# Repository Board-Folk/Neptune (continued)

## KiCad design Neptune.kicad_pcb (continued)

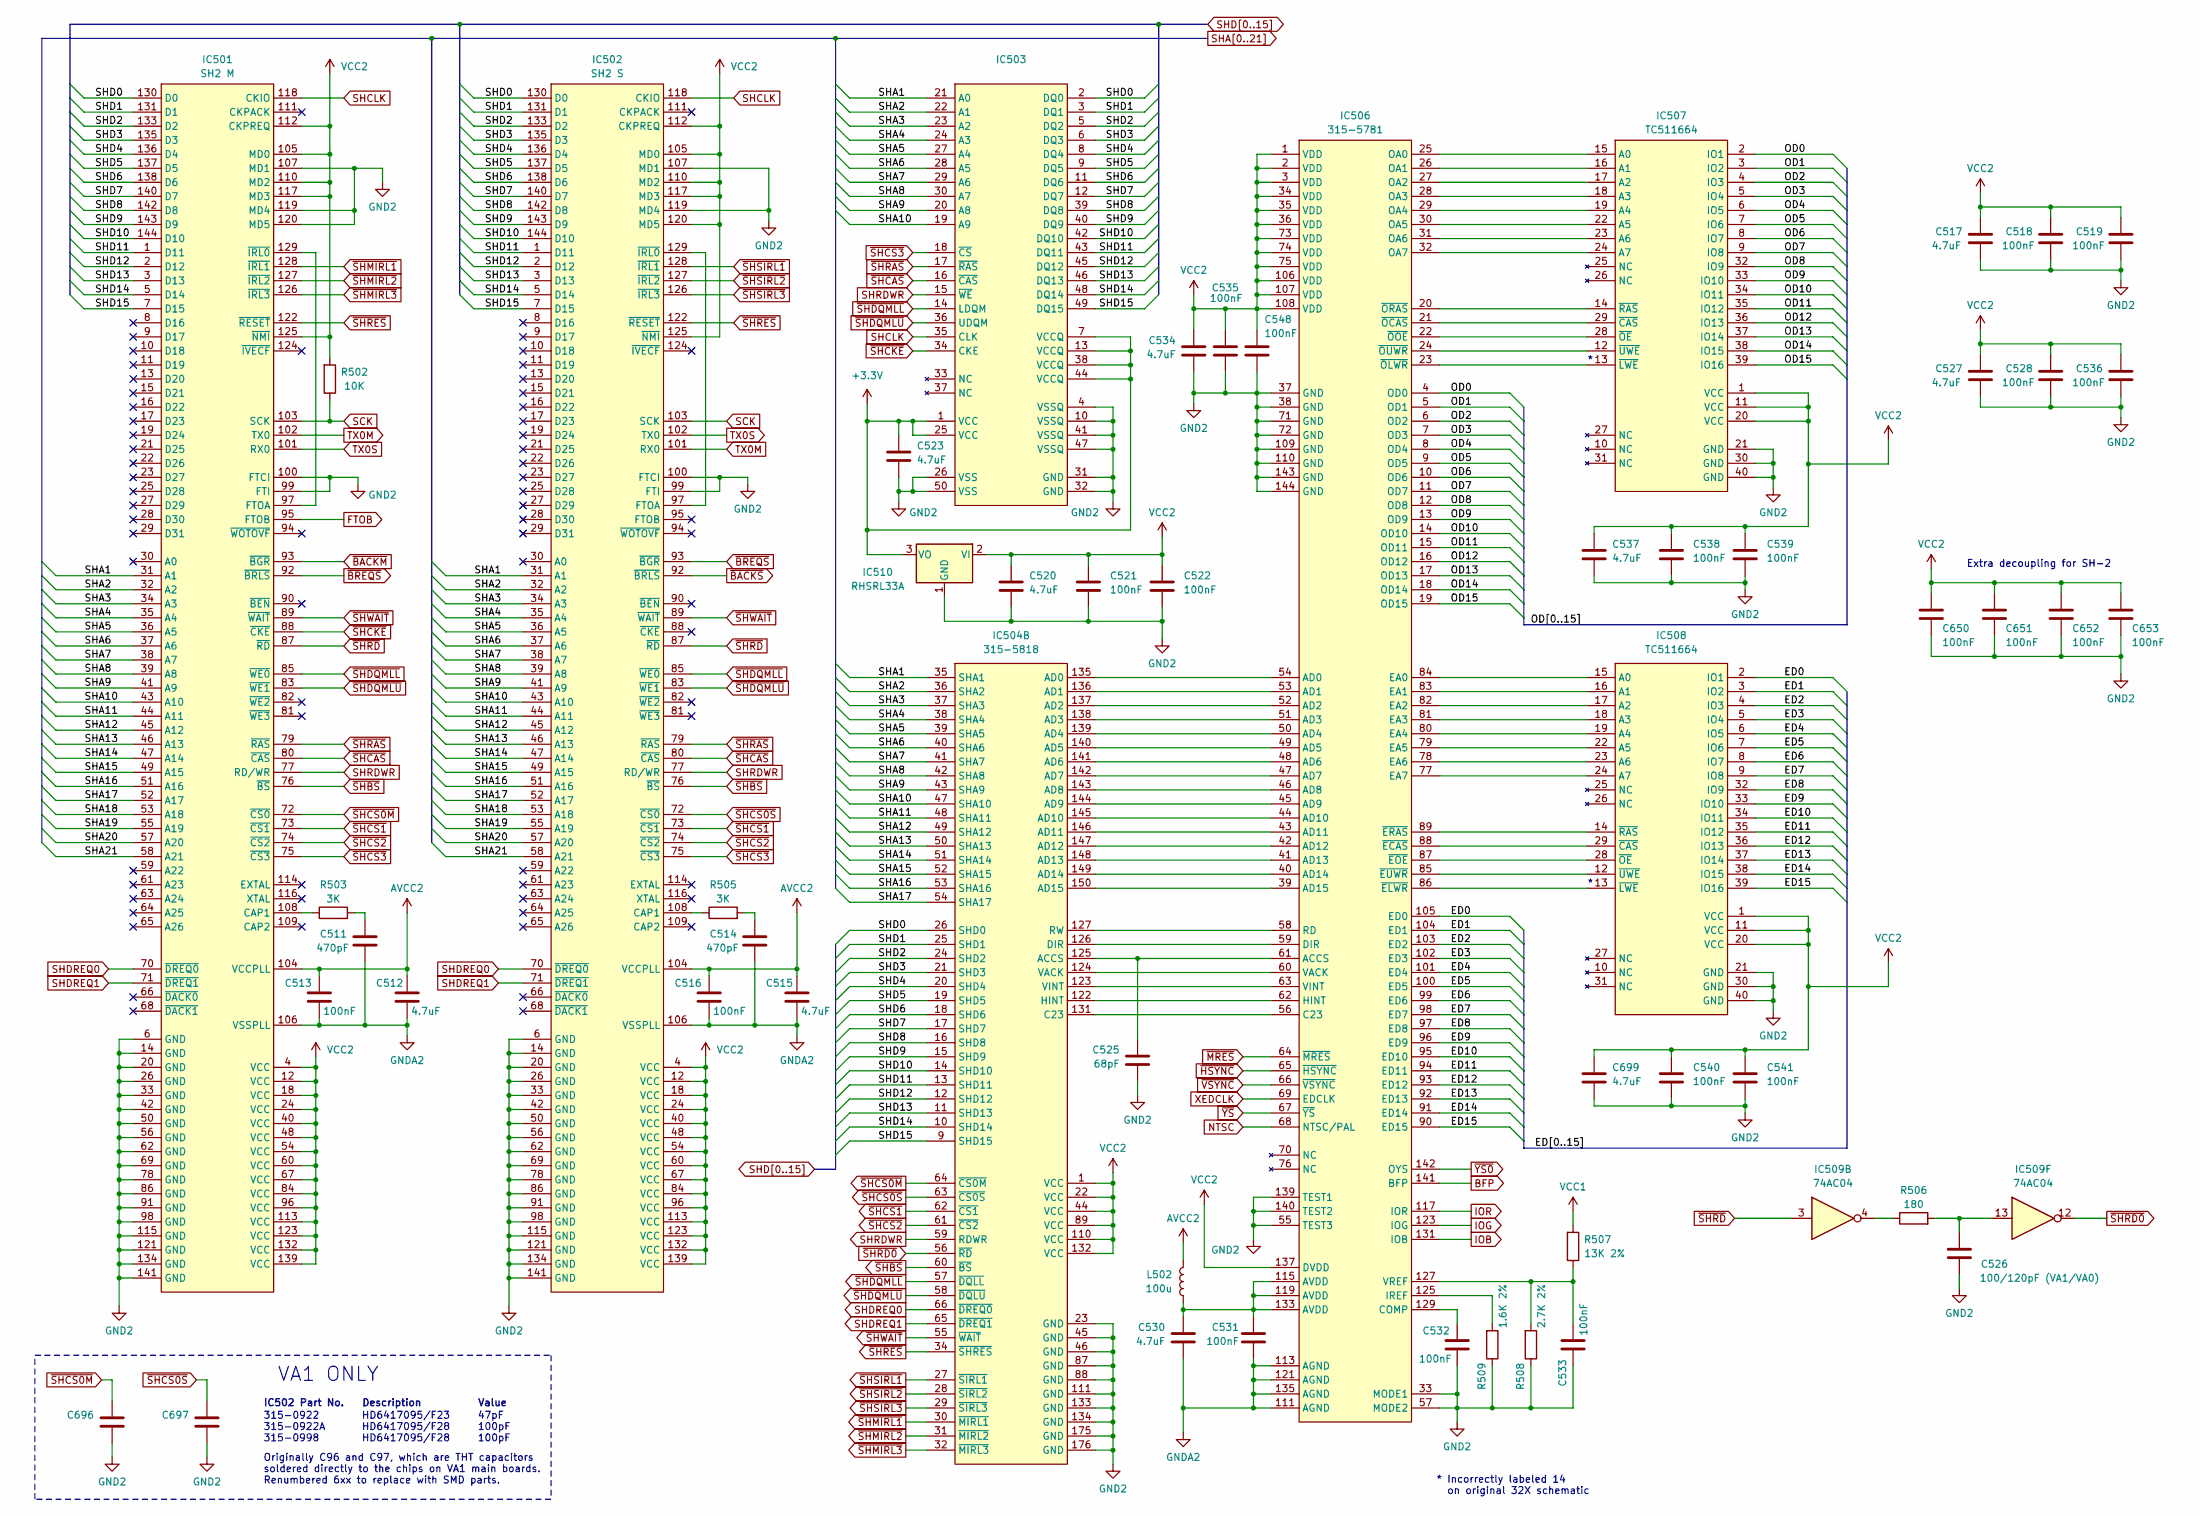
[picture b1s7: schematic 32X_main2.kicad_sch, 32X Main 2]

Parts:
C511, C514: 470pF; C_0805_2012Metric; MPN VJ0805A471FXJPW1BC; LCSC Part # C62771
C512, C515, C517, C520, C523, C527, C530, C534, C537, C699: 4.7uF; C_1206_3216Metric; MPN VJ1206V475MXJTW1BC; LCSC Part # C132170
C513, C516, C518, C519, C521, C522, C528, C531, C532, C533, C535, C536, C538, C539, C540, C541, C548, C650, C651, C652, C653: 100nF; C_0805_2012Metric; MPN VJ0805Y104JXJMT; LCSC Part # C111492
C525: 68pF; C_0805_2012Metric; MPN GRM21A5C2J680JWA1D; LCSC Part # C162306
C526: 100/120pF (VA1/VA0); C_0805_2012Metric; MPN VJ0805A101FXJPW1BC; LCSC Part # C62768
C696, C697: Unused/47/100pF; C_0805_2012Metric; MPN VJ0805A101FXJPW1BC; LCSC Part # C1854109
IC501: SH2 M; LQFP-144_20x20mm_P0.5mm
IC502: SH2 S; LQFP-144_20x20mm_P0.5mm
IC503: µPD4502161; SSOP-50
IC504: 315-5818; LQFP-176_24x24mm_P0.5mm
IC506: 315-5781; LQFP-144_20x20mm_P0.5mm
IC507, IC508: TC511664; SO-Mix-40
IC509: 74AC04; SO-14_Dual_Purpose_P1.27mm; MPN SN74AC04DR; LCSC Part # C352940
IC510: RHSRL33A; SOT-89-3_Handsoldering
L502: 100u; L_1210_3225Metric_Pad1.42x2.65mm_HandSolder; MPN CMI322513J101KT; LCSC Part # C27775
R502: 10K; R_0805_2012Metric; MPN CRCW080510K0FKEA; LCSC Part # C844937
R503, R505: 3K; R_0805_2012Metric; MPN CRCW08053K00FKEA; LCSC Part # C114222
R506: 180; R_0805_2012Metric; MPN CRCW0805180RJNEA; LCSC Part # C137585
R507: 13K 2%; R_0805_2012Metric; MPN CRCW080513K0FKEA; LCSC Part # C844395
R508: 2.7K 2%; R_0805_2012Metric; MPN CRCW08052K70FKEA; LCSC Part # C844836
R509: 1.6K 2%; R_0805_2012Metric; MPN CRCW08051K60FKEA; LCSC Part # C185279

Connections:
+3.3V: C523.1, IC503.1 (VCC), IC503.7 (VCCQ), IC503.13 (VCCQ), IC503.25 (VCC), IC503.38 (VCCQ), IC503.44 (VCCQ), IC510.3 (VO)
/32X Main 2/ED0: IC506.105 (ED0), IC508.2 (IO1)
/32X Main 2/ED1: IC506.104 (ED1), IC508.3 (IO2)
/32X Main 2/ED2: IC506.103 (ED2), IC508.4 (IO3)
/32X Main 2/ED3: IC506.102 (ED3), IC508.5 (IO4)
/32X Main 2/ED4: IC506.101 (ED4), IC508.6 (IO5)
/32X Main 2/ED5: IC506.100 (ED5), IC508.7 (IO6)
/32X Main 2/ED6: IC506.99 (ED6), IC508.8 (IO7)
/32X Main 2/ED7: IC506.98 (ED7), IC508.9 (IO8)
/32X Main 2/ED8: IC506.97 (ED8), IC508.32 (IO9)
/32X Main 2/ED9: IC506.96 (ED9), IC508.33 (IO10)
/32X Main 2/ED10: IC506.95 (ED10), IC508.34 (IO11)
/32X Main 2/ED11: IC506.94 (ED11), IC508.35 (IO12)
/32X Main 2/ED12: IC506.93 (ED12), IC508.36 (IO13)
/32X Main 2/ED13: IC506.92 (ED13), IC508.37 (IO14)
/32X Main 2/ED14: IC506.91 (ED14), IC508.38 (IO15)
/32X Main 2/ED15: IC506.90 (ED15), IC508.39 (IO16)
/32X Main 2/OD0: IC506.4 (OD0), IC507.2 (IO1)
/32X Main 2/OD1: IC506.5 (OD1), IC507.3 (IO2)
/32X Main 2/OD2: IC506.6 (OD2), IC507.4 (IO3)
/32X Main 2/OD3: IC506.7 (OD3), IC507.5 (IO4)
/32X Main 2/OD4: IC506.8 (OD4), IC507.6 (IO5)
/32X Main 2/OD5: IC506.9 (OD5), IC507.7 (IO6)
/32X Main 2/OD6: IC506.10 (OD6), IC507.8 (IO7)
/32X Main 2/OD7: IC506.11 (OD7), IC507.9 (IO8)
/32X Main 2/OD8: IC506.12 (OD8), IC507.32 (IO9)
/32X Main 2/OD9: IC506.13 (OD9), IC507.33 (IO10)
/32X Main 2/OD10: IC506.14 (OD10), IC507.34 (IO11)
/32X Main 2/OD11: IC506.15 (OD11), IC507.35 (IO12)
/32X Main 2/OD12: IC506.16 (OD12), IC507.36 (IO13)
/32X Main 2/OD13: IC506.17 (OD13), IC507.37 (IO14)
/32X Main 2/OD14: IC506.18 (OD14), IC507.38 (IO15)
/32X Main 2/OD15: IC506.19 (OD15), IC507.39 (IO16)
AVCC: C512.1, C513.1, C515.1, C516.1, C517.1, C518.1, C519.1, C520.1, C521.1, C522.1, C527.1, C528.1, C534.1, C535.1, C536.1, C537.1, C538.1, C539.1, C540.1, C541.1, C548.1, C650.1, C651.1, C652.1, C653.1, C699.1, IC501.4 (VCC), IC501.12 (VCC), IC501.18 (VCC), IC501.24 (VCC), IC501.40 (VCC), IC501.48 (VCC), IC501.54 (VCC), IC501.60 (VCC), IC501.67 (VCC), IC501.84 (VCC), IC501.96 (VCC), IC501.104 (VCCPLL), IC501.105 (MD0), IC501.110 (MD2), IC501.112 (CKPREQ), IC501.113 (VCC), IC501.117 (MD3), IC501.123 (VCC), IC501.125 (~NMI), IC501.132 (VCC), IC501.139 (VCC), IC502.4 (VCC), IC502.12 (VCC), IC502.18 (VCC), IC502.24 (VCC), IC502.40 (VCC), IC502.48 (VCC), IC502.54 (VCC), IC502.60 (VCC), IC502.67 (VCC), IC502.84 (VCC), IC502.96 (VCC), IC502.104 (VCCPLL), IC502.105 (MD0), IC502.110 (MD2), IC502.112 (CKPREQ), IC502.113 (VCC), IC502.117 (MD3), IC502.120 (MD5), IC502.123 (VCC), IC502.125 (~NMI), IC502.132 (VCC), IC502.139 (VCC), IC504.1 (VCC), IC504.22 (VCC), IC504.44 (VCC), IC504.89 (VCC), IC504.110 (VCC), IC504.132 (VCC), IC506.1 (VDD), IC506.2 (VDD), IC506.3 (VDD), IC506.34 (VDD), IC506.35 (VDD), IC506.36 (VDD), IC506.73 (VDD), IC506.74 (VDD), IC506.75 (VDD), IC506.106 (VDD), IC506.107 (VDD), IC506.108 (VDD), IC506.137 (DVDD), IC507.1 (VCC), IC507.11 (VCC), IC507.20 (VCC), IC508.1 (VCC), IC508.11 (VCC), IC508.20 (VCC), IC510.2 (VI), L502.1, R502.2, R507.2; also elsewhere on the board
BFP: IC506.141 (BFP); also elsewhere on the board
FTOB: IC501.95 (FTOB); also elsewhere on the board
GND: C511.2, C512.2, C513.2, C514.2, C515.2, C516.2, C517.2, C518.2, C519.2, C520.2, C521.2, C522.2, C523.2, C525.2, C526.2, C527.2, C528.2, C530.2, C531.2, C532.2, C533.2, C534.2, C535.2, C536.2, C537.2, C538.2, C539.2, C540.2, C541.2, C548.2, C650.2, C651.2, C652.2, C653.2, C696.2, C697.2, C699.2, IC501.6 (GND), IC501.14 (GND), IC501.20 (GND), IC501.26 (GND), IC501.33 (GND), IC501.42 (GND), IC501.50 (GND), IC501.56 (GND), IC501.62 (GND), IC501.69 (GND), IC501.78 (GND), IC501.86 (GND), IC501.91 (GND), IC501.98 (GND), IC501.99 (FTI), IC501.100 (FTCI), IC501.106 (VSSPLL), IC501.107 (MD1), IC501.115 (GND), IC501.119 (MD4), IC501.120 (MD5), IC501.121 (GND), IC501.134 (GND), IC501.141 (GND), IC502.6 (GND), IC502.14 (GND), IC502.20 (GND), IC502.26 (GND), IC502.33 (GND), IC502.42 (GND), IC502.50 (GND), IC502.56 (GND), IC502.62 (GND), IC502.69 (GND), IC502.78 (GND), IC502.86 (GND), IC502.91 (GND), IC502.98 (GND), IC502.99 (FTI), IC502.100 (FTCI), IC502.106 (VSSPLL), IC502.107 (MD1), IC502.115 (GND), IC502.119 (MD4), IC502.121 (GND), IC502.134 (GND), IC502.141 (GND), IC503.4 (VSSQ), IC503.10 (VSSQ), IC503.26 (VSS), IC503.31 (GND), IC503.32 (GND), IC503.41 (VSSQ), IC503.47 (VSSQ), IC503.50 (VSS), IC504.23 (GND), IC504.45 (GND), IC504.46 (GND), IC504.87 (GND), IC504.88 (GND), IC504.111 (GND), IC504.133 (GND), IC504.134 (GND), IC504.175 (GND), IC504.176 (GND), IC506.33 (MODE1), IC506.37 (GND), IC506.38 (GND), IC506.55 (TEST3), IC506.57 (MODE2), IC506.71 (GND), IC506.72 (GND), IC506.109 (GND), IC506.110 (GND), IC506.111 (AGND), IC506.113 (AGND), IC506.121 (AGND), IC506.135 (AGND), IC506.139 (TEST1), IC506.140 (TEST2), IC506.143 (GND), IC506.144 (GND), IC507.21 (GND), IC507.30 (GND), IC507.40 (GND), IC508.21 (GND), IC508.30 (GND), IC508.40 (GND), IC510.1 (GND), R508.1, R509.1; also elsewhere on the board
IOB: IC506.131 (IOB); also elsewhere on the board
IOG: IC506.123 (IOG); also elsewhere on the board
IOR: IC506.117 (IOR); also elsewhere on the board
NTSC: IC506.68 (NTSC/PAL); also elsewhere on the board
unnamed: C511.1, R503.2
unnamed: C514.1, R505.2
unnamed: C526.1, IC509.13, R506.2
unnamed: C530.1, C531.1, IC506.115 (AVDD), IC506.119 (AVDD), IC506.133 (AVDD), L502.2
unnamed: IC501.108 (CAP1), R503.1
unnamed: IC501.97 (FTOA), IC501.129 (~IRL0)
unnamed: IC502.108 (CAP1), R505.1
unnamed: IC502.97 (FTOA), IC502.129 (~IRL0)
unnamed: C525.1, IC504.125 (ACCS), IC506.61 (ACCS)
unnamed: IC504.135 (AD0), IC506.54 (AD0)
unnamed: IC504.136 (AD1), IC506.53 (AD1)
unnamed: IC504.137 (AD2), IC506.52 (AD2)
unnamed: IC504.138 (AD3), IC506.51 (AD3)
unnamed: IC504.139 (AD4), IC506.50 (AD4)
unnamed: IC504.140 (AD5), IC506.49 (AD5)
unnamed: IC504.141 (AD6), IC506.48 (AD6)
unnamed: IC504.142 (AD7), IC506.47 (AD7)
unnamed: IC504.143 (AD8), IC506.46 (AD8)
unnamed: IC504.144 (AD9), IC506.45 (AD9)
unnamed: IC504.145 (AD10), IC506.44 (AD10)
unnamed: IC504.146 (AD11), IC506.43 (AD11)
unnamed: IC504.147 (AD12), IC506.42 (AD12)
unnamed: IC504.148 (AD13), IC506.41 (AD13)
unnamed: IC504.149 (AD14), IC506.40 (AD14)
unnamed: IC504.150 (AD15), IC506.39 (AD15)
unnamed: IC504.131 (C23), IC506.56 (C23)
unnamed: IC504.126 (DIR), IC506.59 (DIR)
unnamed: IC504.122 (HINT), IC506.62 (HINT)
unnamed: IC504.127 (RW), IC506.58 (RD)
unnamed: IC504.124 (VACK), IC506.60 (VACK)
unnamed: IC504.123 (VINT), IC506.63 (VINT)
unnamed: C532.1, IC506.129 (COMP)
unnamed: IC506.84 (EA0), IC508.15 (A0)
unnamed: IC506.83 (EA1), IC508.16 (A1)
unnamed: IC506.82 (EA2), IC508.17 (A2)
unnamed: IC506.81 (EA3), IC508.18 (A3)
unnamed: IC506.80 (EA4), IC508.19 (A4)
unnamed: IC506.79 (EA5), IC508.22 (A5)
unnamed: IC506.78 (EA6), IC508.23 (A6)
unnamed: IC506.77 (EA7), IC508.24 (A7)
unnamed: IC506.125 (IREF), R509.2
unnamed: IC506.25 (OA0), IC507.15 (A0)
unnamed: IC506.26 (OA1), IC507.16 (A1)
unnamed: IC506.27 (OA2), IC507.17 (A2)
unnamed: IC506.28 (OA3), IC507.18 (A3)
unnamed: IC506.29 (OA4), IC507.19 (A4)
unnamed: IC506.30 (OA5), IC507.22 (A5)
unnamed: IC506.31 (OA6), IC507.23 (A6)
unnamed: IC506.32 (OA7), IC507.24 (A7)
unnamed: C533.1, IC506.127 (VREF), R507.1, R508.2
unnamed: IC506.88 (~ECAS), IC508.29 (~CAS)
unnamed: IC506.86 (~ELWR), IC508.13 (~LWE)
unnamed: IC506.87 (~EOE), IC508.28 (~OE)
unnamed: IC506.89 (~ERAS), IC508.14 (~RAS)
unnamed: IC506.85 (~EUWR), IC508.12 (~UWE)
unnamed: IC506.21 (~OCAS), IC507.29 (~CAS)
unnamed: IC506.23 (~OLWR), IC507.13 (~LWE)
unnamed: IC506.22 (~OOE), IC507.28 (~OE)
unnamed: IC506.20 (~ORAS), IC507.14 (~RAS)
unnamed: IC506.24 (~OUWR), IC507.12 (~UWE)
unnamed: IC509.4, R506.1
SCK: IC501.103 (SCK), IC502.103 (SCK), R502.1
SHA1: IC501.31 (A1), IC502.31 (A1), IC503.21 (A0), IC504.35 (SHA1); also elsewhere on the board
SHA2: IC501.32 (A2), IC502.32 (A2), IC503.22 (A1), IC504.36 (SHA2); also elsewhere on the board
SHA3: IC501.34 (A3), IC502.34 (A3), IC503.23 (A2), IC504.37 (SHA3); also elsewhere on the board
SHA4: IC501.35 (A4), IC502.35 (A4), IC503.24 (A3), IC504.38 (SHA4); also elsewhere on the board
SHA5: IC501.36 (A5), IC502.36 (A5), IC503.27 (A4), IC504.39 (SHA5); also elsewhere on the board
SHA6: IC501.37 (A6), IC502.37 (A6), IC503.28 (A5), IC504.40 (SHA6); also elsewhere on the board
SHA7: IC501.38 (A7), IC502.38 (A7), IC503.29 (A6), IC504.41 (SHA7); also elsewhere on the board
SHA8: IC501.39 (A8), IC502.39 (A8), IC503.30 (A7), IC504.42 (SHA8); also elsewhere on the board
SHA9: IC501.41 (A9), IC502.41 (A9), IC503.20 (A8), IC504.43 (SHA9); also elsewhere on the board
SHA10: IC501.43 (A10), IC502.43 (A10), IC503.19 (A9), IC504.47 (SHA10); also elsewhere on the board
SHA11: IC501.44 (A11), IC502.44 (A11), IC504.48 (SHA11); also elsewhere on the board
SHA12: IC501.45 (A12), IC502.45 (A12), IC504.49 (SHA12); also elsewhere on the board
SHA13: IC501.46 (A13), IC502.46 (A13), IC504.50 (SHA13); also elsewhere on the board
SHA14: IC501.47 (A14), IC502.47 (A14), IC504.51 (SHA14); also elsewhere on the board
SHA15: IC501.49 (A15), IC502.49 (A15), IC504.52 (SHA15); also elsewhere on the board
SHA16: IC501.51 (A16), IC502.51 (A16), IC504.53 (SHA16); also elsewhere on the board
SHA17: IC501.52 (A17), IC502.52 (A17), IC504.54 (SHA17); also elsewhere on the board
SHA18: IC501.53 (A18), IC502.53 (A18); also elsewhere on the board
SHA19: IC501.55 (A19), IC502.55 (A19); also elsewhere on the board
SHA20: IC501.57 (A20), IC502.57 (A20); also elsewhere on the board
SHA21: IC501.58 (A21), IC502.58 (A21); also elsewhere on the board
SHCLK: IC501.118 (CKIO), IC502.118 (CKIO), IC503.35 (CLK); also elsewhere on the board
SHD0: IC501.130 (D0), IC502.130 (D0), IC503.2 (DQ0), IC504.26 (SHD0)
SHD1: IC501.131 (D1), IC502.131 (D1), IC503.3 (DQ1), IC504.25 (SHD1)
SHD2: IC501.133 (D2), IC502.133 (D2), IC503.5 (DQ2), IC504.24 (SHD2)
SHD3: IC501.135 (D3), IC502.135 (D3), IC503.6 (DQ3), IC504.21 (SHD3)
SHD4: IC501.136 (D4), IC502.136 (D4), IC503.8 (DQ4), IC504.20 (SHD4)
SHD5: IC501.137 (D5), IC502.137 (D5), IC503.9 (DQ5), IC504.19 (SHD5)
SHD6: IC501.138 (D6), IC502.138 (D6), IC503.11 (DQ6), IC504.18 (SHD6)
SHD7: IC501.140 (D7), IC502.140 (D7), IC503.12 (DQ7), IC504.17 (SHD7)
SHD8: IC501.142 (D8), IC502.142 (D8), IC503.39 (DQ8), IC504.16 (SHD8)
SHD9: IC501.143 (D9), IC502.143 (D9), IC503.40 (DQ9), IC504.15 (SHD9)
SHD10: IC501.144 (D10), IC502.144 (D10), IC503.42 (DQ10), IC504.14 (SHD10)
SHD11: IC501.1 (D11), IC502.1 (D11), IC503.43 (DQ11), IC504.13 (SHD11)
SHD12: IC501.2 (D12), IC502.2 (D12), IC503.45 (DQ12), IC504.12 (SHD12)
SHD13: IC501.3 (D13), IC502.3 (D13), IC503.46 (DQ13), IC504.11 (SHD13)
SHD14: IC501.5 (D14), IC502.5 (D14), IC503.48 (DQ14), IC504.10 (SHD14)
SHD15: IC501.7 (D15), IC502.7 (D15), IC503.49 (DQ15), IC504.9 (SHD15)
SHDREQ0: IC501.70 (~DREQ0), IC502.70 (~DREQ0), IC504.66 (~DREQ0)
SHDREQ1: IC501.71 (~DREQ1), IC502.71 (~DREQ1), IC504.65 (~DREQ1)
SHRDWR: IC501.77 (RD/WR), IC502.77 (RD/WR), IC503.15 (~WE), IC504.59 (RDWR)
TX0M: IC501.102 (TX0), IC502.101 (RX0)
TX0S: IC501.101 (RX0), IC502.102 (TX0)
XEDCLK: IC506.69 (EDCLK); also elsewhere on the board
~BACKM: IC501.93 (~BGR); also elsewhere on the board
~BACKS: IC502.92 (~BRLS); also elsewhere on the board
~BREQS: IC501.92 (~BRLS), IC502.93 (~BGR); also elsewhere on the board
~HSYNC: IC506.65 (~HSYNC); also elsewhere on the board
~MRES: IC506.64 (~MRES); also elsewhere on the board
~SHBS: IC501.76 (~BS), IC502.76 (~BS), IC504.60 (~BS)
~SHCAS: IC501.80 (~CAS), IC502.80 (~CAS), IC503.16 (~CAS)
~SHCKE: IC501.88 (~CKE), IC503.34 (CKE)
~SHCS0M: C696.1, IC501.72 (~CS0), IC504.64 (~CS0M)
~SHCS0S: C697.1, IC502.72 (~CS0), IC504.63 (~CS0S)
~SHCS1: IC501.73 (~CS1), IC502.73 (~CS1), IC504.62 (~CS1)
~SHCS2: IC501.74 (~CS2), IC502.74 (~CS2), IC504.61 (~CS2)
~SHCS3: IC501.75 (~CS3), IC502.75 (~CS3), IC503.18 (~CS)
~SHDQMLL: IC501.85 (~WE0), IC502.85 (~WE0), IC503.14 (LDQM), IC504.57 (~DQLL)
~SHDQMLU: IC501.83 (~WE1), IC502.83 (~WE1), IC503.36 (UDQM), IC504.58 (~DQLU)
~SHMIRL1: IC501.128 (~IRL1), IC504.30 (~MIRL1)
~SHMIRL2: IC501.127 (~IRL2), IC504.31 (~MIRL2)
~SHMIRL3: IC501.126 (~IRL3), IC504.32 (~MIRL3)
~SHRAS: IC501.79 (~RAS), IC502.79 (~RAS), IC503.17 (~RAS)
~SHRD0: IC504.56 (~RD), IC509.12
~SHRD: IC501.87 (~RD), IC502.87 (~RD), IC509.3
~SHRES: IC501.122 (~RESET), IC502.122 (~RESET), IC504.34 (~SHRES)
~SHSIRL1: IC502.128 (~IRL1), IC504.27 (~SIRL1)
~SHSIRL2: IC502.127 (~IRL2), IC504.28 (~SIRL2)
~SHSIRL3: IC502.126 (~IRL3), IC504.29 (~SIRL3)
~SHWAIT: IC501.89 (~WAIT), IC502.89 (~WAIT), IC504.55 (~WAIT)
~VSYNC: IC506.66 (~VSYNC); also elsewhere on the board
~YS0: IC506.142 (OYS); also elsewhere on the board
~YS: IC506.67 (~YS); also elsewhere on the board

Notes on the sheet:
315-0922 315-0922A 315-0998
* Incorrectly labeled 14 on original 32X schematic
VA1 ONLY
IC502 Part No.
Value
Description
47pF 100pF 100pF
Extra decoupling for SH-2
Originally C96 and C97, which are THT capacitors soldered directly to the chips on VA1 main boards. Renumbered 6xx to replace with SMD parts.
HD6417095/F23 HD6417095/F28 HD6417095/F28

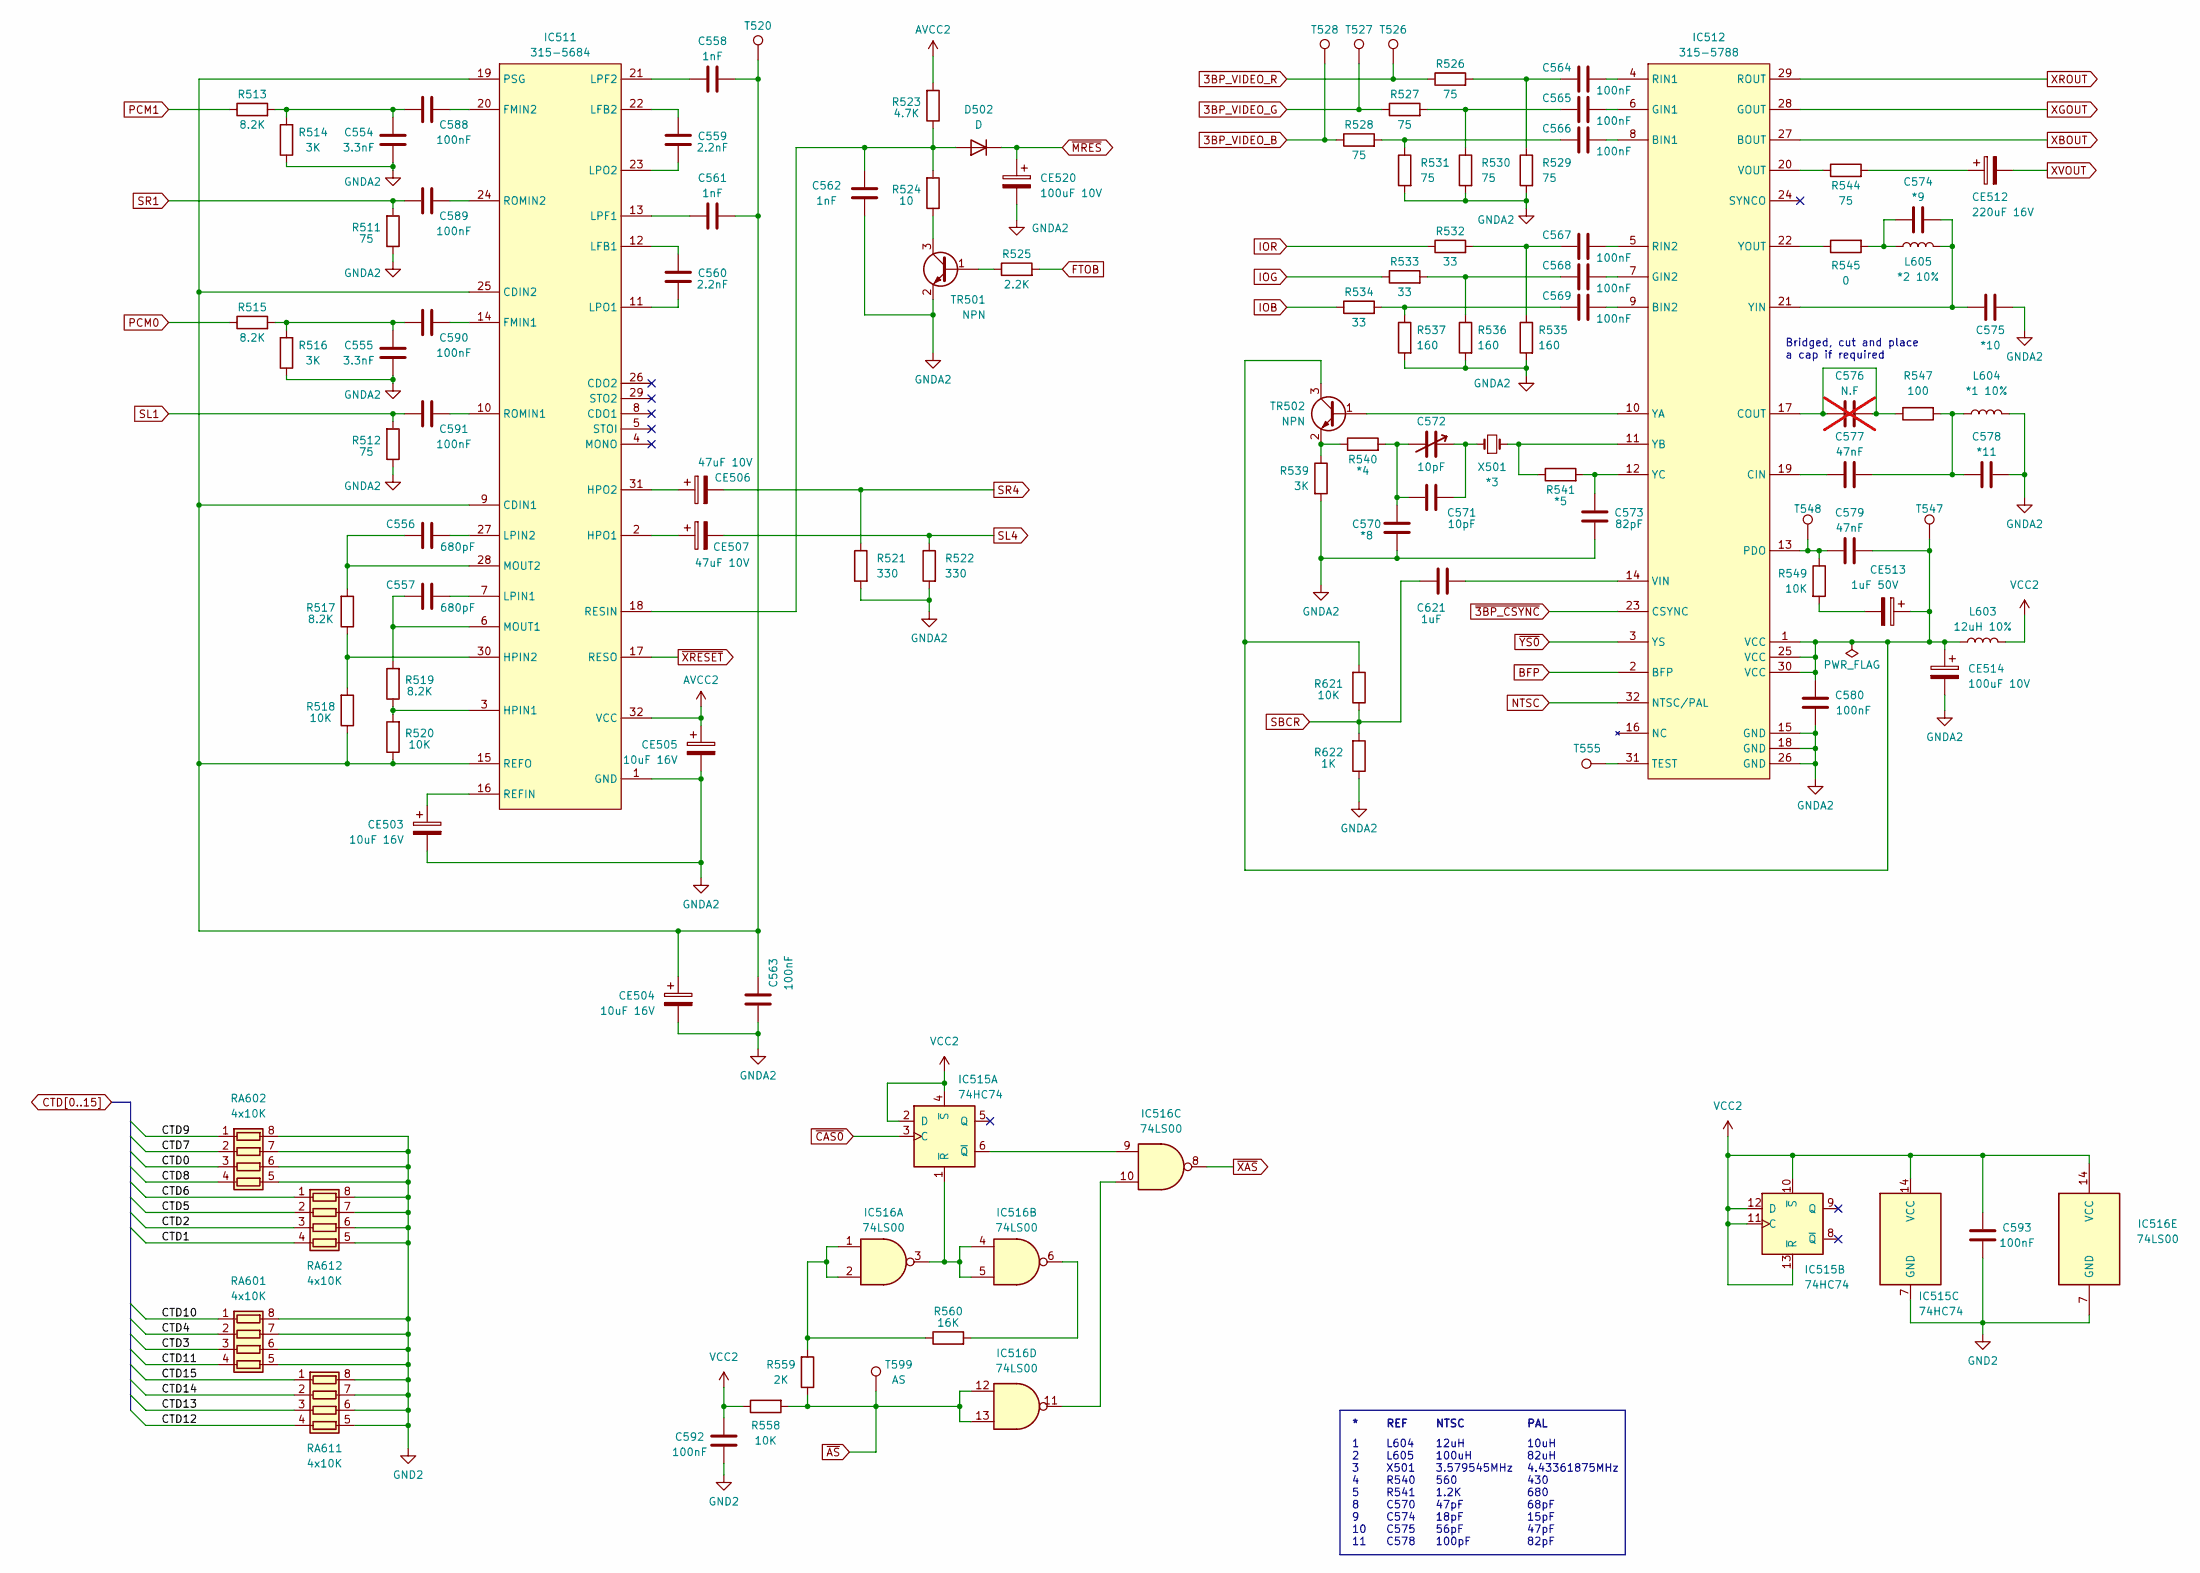
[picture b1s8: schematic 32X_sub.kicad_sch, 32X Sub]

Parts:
C554, C555: 3.3nF; C_0805_2012Metric; MPN VJ0805A332FXJTW1BC; LCSC Part # C107149
C556, C557: 680pF; C_0805_2012Metric; MPN VJ0805A681FXJCW1BC; LCSC Part # C107121
C558, C561, C562: 1nF; C_0805_2012Metric; MPN VJ0805A102FXJCW1BC; LCSC Part # C62774
C559, C560: 2.2nF; C_0805_2012Metric; MPN VJ0805A222FXJCW1BC; LCSC Part # C107103
C563, C564, C565, C566, C567, C568, C569, C580, C588, C589, C590, C591, C592, C593: 100nF; C_0805_2012Metric; MPN VJ0805Y104JXJMT; LCSC Part # C111492
C570: *8; C_0805_2012Metric; MPN GRM21A5C2J680JWA1D; LCSC Part # C162306
C571: 10pF; C_0805_2012Metric; MPN VJ0805A100FXJCW1BC; LCSC Part # C520053
C572: 10pF; C_Rect_L7.0mm_W6.5mm_P5.00mm
C573: 82pF; C_0805_2012Metric; MPN VJ0805A820FXJCW1BC; LCSC Part # C327193
C574: *9; C_0805_2012Metric; MPN CC0805JRNPOCBN150; LCSC Part # C527077
C575: *10; C_0805_2012Metric; MPN GRM21A5C2E470JW01D; LCSC Part # C437549
C576: N.F; C_0805_2012Metric; not fitted
C577, C579: 47nF; C_0805_2012Metric; MPN VJ0805Y473JXJCW1BC; LCSC Part # C107154
C578: *11; C_0805_2012Metric; MPN GRM21A5C2E820JW01D; LCSC Part # C710971
C621: 1uF; C_0805_2012Metric; MPN VJ0805Y105KXJTW1BC; LCSC Part # C541528
CE503, CE504, CE505: 10uF 16V; CP_Radial_D5.0mm_P2.50mm
CE506, CE507: 47uF 10V; CP_Radial_D5.0mm_P2.50mm; DigiKey 493-13447-1-ND
CE512: 220uF 16V; CP_Radial_D5.0mm_P2.50mm
CE513: 1uF 50V; CP_Radial_D5.0mm_P2.50mm
CE514, CE520: 100uF 10V; CP_Radial_D5.0mm_P2.50mm
D502: D; D_T-1_P5.08mm_Horizontal
IC511: 315-5684; SO-32-0.8mm
IC512: 315-5788; SO-32-0.8mm
IC515: 74HC74; SO-14_Dual_Purpose_P1.27mm; MPN SN74HC74ANS; LCSC Part # C6762
IC516: 74LS00; SO-14_Dual_Purpose_P1.27mm; MPN SN74LS00NSR; LCSC Part # C140269
L603: 12uH 10%; L_1210_3225Metric_Pad1.42x2.65mm_HandSolder; MPN CMI322513X120KT; LCSC Part # C394998
L604: *1 10%; L_1210_3225Metric_Pad1.42x2.65mm_HandSolder; MPN FHW1210IF100JST; LCSC Part # C75643
L605: *2 10%; L_1210_3225Metric_Pad1.42x2.65mm_HandSolder; MPN FHW1210IF820JST; LCSC Part # C394099
R511, R512, R544: 75; R_0805_2012Metric; MPN CRCW080575R0FKEAHP; DigiKey P75.0CCT-ND
R513, R515, R517, R519: 8.2K; R_0805_2012Metric; MPN CRCW08058K20FKEA; LCSC Part # C844640
R514, R516, R539: 3K; R_0805_2012Metric; MPN CRCW08053K00FKEA; LCSC Part # C114222
R518, R520, R549, R558, R621: 10K; R_0805_2012Metric; MPN CRCW080510K0FKEA; LCSC Part # C844937
R521, R522: 330; R_0805_2012Metric; MPN CRCW0805330RFKEA; LCSC Part # C844839
R523: 4.7K; R_0805_2012Metric; MPN CRCW08054K70JNEAC; LCSC Part # C2077067
R524: 10; R_0805_2012Metric; MPN CRCW080510R0FKEB; LCSC Part # C96347
R525: 2.2K; R_0805_2012Metric; MPN CRCW08052K20JNEA; DigiKey P2.20KCCT-ND
R526, R527, R528: 75; R_0805_2012Metric; MPN CRCW080575R0FKEAHP; DigiKey P5.62KCCT-ND
R529, R530, R531: 75; R_0805_2012Metric; MPN CRCW080575R0FKEAHP; DigiKey P1.00KCCT-ND
R532, R533, R534: 33; R_0805_2012Metric; MPN CRCW080533R0FKEAC; LCSC Part # C126353
R535, R536, R537: 160; R_0805_2012Metric; MPN MCU08050C1600FPW00; LCSC Part # C246032
R540: *4; R_0805_2012Metric; MPN CRCW0805430RJNEA; LCSC Part # C137527
R541: *5; R_0805_2012Metric; MPN CRCW0805680RJNEA; LCSC Part # C93658
R545: 0; R_0805_2012Metric; MPN RCG08050000Z0EA; LCSC Part # C96345
R547: 100; R_0805_2012Metric; MPN CRCW0805100RJNEAHP; LCSC Part # C2078104
R559: 2K; R_0805_2012Metric; MPN CRCW08052K00JNEA; LCSC Part # C2077049
R560: 16K; R_0805_2012Metric; MPN TNPW080516K0BEEA; LCSC Part # C326942
R622: 1K; R_0805_2012Metric; MPN CRCW08051K00FKEA; LCSC Part # C136899
RA601, RA602, RA611, RA612: 4x10K; R_Array_Convex_4x0603; MPN YC164-FR-0710KL; LCSC Part # C110924
T520, T526, T527, T528, T547, T548, T555: TestPoint
T599: AS
TR501: NPN; SOT-23-3; MPN MMBT3904-TP; LCSC Part # C77991
TR502: NPN; SOT-23; MPN MMBT3904-TP; LCSC Part # C77991
X501: *3; Crystal_HC18-U_Vertical

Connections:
3BP_VIDEO_B: R528.1, T528.1; also elsewhere on the board
3BP_VIDEO_G: R527.1, T527.1; also elsewhere on the board
3BP_VIDEO_R: R526.1, T526.1; also elsewhere on the board
AVCC: C592.2, C593.1, CE505.1, IC511.32 (VCC), IC515.2 (D), IC515.4 (~S), IC515.10 (~S), IC515.11 (C), IC515.12 (D), IC515.13 (~R), IC515.14 (VCC), IC516.14 (VCC), L603.2, R523.2, R558.1; also elsewhere on the board
BFP: IC512.2 (BFP); also elsewhere on the board
CTD0: RA602.3 (R3.1); also elsewhere on the board
CTD1: RA612.4 (R4.1); also elsewhere on the board
CTD2: RA612.3 (R3.1); also elsewhere on the board
CTD3: RA601.3 (R3.1); also elsewhere on the board
CTD4: RA601.2 (R2.1); also elsewhere on the board
CTD5: RA612.2 (R2.1); also elsewhere on the board
CTD6: RA612.1 (R1.1); also elsewhere on the board
CTD7: RA602.2 (R2.1); also elsewhere on the board
CTD8: RA602.4 (R4.1); also elsewhere on the board
CTD9: RA602.1 (R1.1); also elsewhere on the board
CTD10: RA601.1 (R1.1); also elsewhere on the board
CTD11: RA601.4 (R4.1); also elsewhere on the board
CTD12: RA611.4 (R4.1); also elsewhere on the board
CTD13: RA611.3 (R3.1); also elsewhere on the board
CTD14: RA611.2 (R2.1); also elsewhere on the board
CTD15: RA611.1 (R1.1); also elsewhere on the board
FTOB: R525.2; also elsewhere on the board
GND: C554.2, C555.2, C562.1, C563.1, C570.1, C573.1, C575.2, C578.2, C580.1, C592.1, C593.2, CE503.2, CE504.2, CE505.2, CE514.2, CE520.2, IC511.1 (GND), IC512.15 (GND), IC512.18 (GND), IC512.26 (GND), IC515.7 (GND), IC516.7 (GND), L604.2, R511.1, R512.1, R514.1, R516.1, R521.2, R522.2, R529.2, R530.2, R531.2, R535.2, R536.2, R537.2, R539.2, R622.1, RA601.5 (R4.2), RA601.6 (R3.2), RA601.7 (R2.2), RA601.8 (R1.2), RA602.5 (R4.2), RA602.6 (R3.2), RA602.7 (R2.2), RA602.8 (R1.2), RA611.5 (R4.2), RA611.6 (R3.2), RA611.7 (R2.2), RA611.8 (R1.2), RA612.5 (R4.2), RA612.6 (R3.2), RA612.7 (R2.2), RA612.8 (R1.2), TR501.2 (E); also elsewhere on the board
IOB: R534.1; also elsewhere on the board
IOG: R533.1; also elsewhere on the board
IOR: R532.1; also elsewhere on the board
NTSC: IC512.32 (NTSC/PAL); also elsewhere on the board
unnamed: C554.1, C588.1, R513.2, R514.2
unnamed: C555.1, C590.1, R515.2, R516.2
unnamed: C564.1, R526.2, R529.1
unnamed: C565.1, R527.2, R530.1
unnamed: C566.1, R528.2, R531.1
unnamed: C567.1, R532.2, R535.1
unnamed: C568.1, R533.2, R536.1
unnamed: C569.1, R534.2, R537.1
unnamed: C570.2, C571.1, C572.2, R540.2
unnamed: C571.2, C572.1, X501.1
unnamed: C574.1, L605.1, R545.2
unnamed: C577.2, C578.1, L604.1, R547.2
unnamed: CE512.1, R544.2
unnamed: CE513.2, R549.2
unnamed: C562.2, D502.2 (A), IC511.18 (RESIN), R523.1, R524.2
unnamed: C558.2, C561.2, C563.2, CE504.1, IC511.9 (CDIN1), IC511.15 (REFO), IC511.19 (PSG), IC511.25 (CDIN2), R518.1, R520.1, T520.1
unnamed: C590.2, IC511.14 (FMIN1)
unnamed: C588.2, IC511.20 (FMIN2)
unnamed: IC511.3 (HPIN1), R519.1, R520.2
unnamed: IC511.30 (HPIN2), R517.1, R518.2
unnamed: CE507.1, IC511.2 (HPO1)
unnamed: CE506.1, IC511.31 (HPO2)
unnamed: C560.2, IC511.12 (LFB1)
unnamed: C559.2, IC511.22 (LFB2)
unnamed: C561.1, IC511.13 (LPF1)
unnamed: C558.1, IC511.21 (LPF2)
unnamed: C557.2, IC511.7 (LPIN1)
unnamed: C556.2, IC511.27 (LPIN2)
unnamed: C560.1, IC511.11 (LPO1)
unnamed: C559.1, IC511.23 (LPO2)
unnamed: C557.1, IC511.6 (MOUT1), R519.2
unnamed: C556.1, IC511.28 (MOUT2), R517.2
unnamed: CE503.1, IC511.16 (REFIN)
unnamed: C591.2, IC511.10 (ROMIN1)
unnamed: C589.2, IC511.24 (ROMIN2)
unnamed: C566.2, IC512.8 (BIN1)
unnamed: C569.2, IC512.9 (BIN2)
unnamed: C577.1, IC512.19 (CIN)
unnamed: C576.1, C576.2, IC512.17 (COUT), R547.1
unnamed: C565.2, IC512.6 (GIN1)
unnamed: C568.2, IC512.7 (GIN2)
unnamed: C579.1, IC512.13 (PDO), R549.1, T548.1
unnamed: C564.2, IC512.4 (RIN1)
unnamed: C567.2, IC512.5 (RIN2)
unnamed: IC512.31 (TEST), T555.1
unnamed: C621.2, IC512.14 (VIN)
unnamed: IC512.20 (VOUT), R544.1
unnamed: IC512.10 (YA), TR502.1 (B)
unnamed: IC512.11 (YB), R541.1, X501.2
unnamed: C573.2, IC512.12 (YC), R541.2
unnamed: C574.2, C575.1, IC512.21 (YIN), L605.2
unnamed: IC512.22 (YOUT), R545.1
unnamed: IC515.6 (~Q), IC516.9
unnamed: IC515.1 (~R), IC516.3, IC516.4, IC516.5
unnamed: IC516.1, IC516.2, R559.2, R560.1
unnamed: IC516.6, R560.2
unnamed: IC516.10, IC516.11
unnamed: R525.1, TR501.1 (B)
unnamed: R524.1, TR501.3 (C)
unnamed: C579.2, C580.2, CE513.1, CE514.1, IC512.1 (VCC), IC512.25 (VCC), IC512.30 (VCC), L603.1, R621.2, T547.1, TR502.3 (C)
unnamed: R539.1, R540.1, TR502.2 (E)
PCM0: R515.1; also elsewhere on the board
PCM1: R513.1; also elsewhere on the board
SBCR: C621.1, R621.1, R622.2; also elsewhere on the board
SL1: C591.1, R512.2; also elsewhere on the board
SL4: CE507.2, R522.1; also elsewhere on the board
SR1: C589.1, R511.2; also elsewhere on the board
SR4: CE506.2, R521.1; also elsewhere on the board
XBOUT: IC512.27 (BOUT); also elsewhere on the board
XGOUT: IC512.28 (GOUT); also elsewhere on the board
XROUT: IC512.29 (ROUT); also elsewhere on the board
XVOUT: CE512.2; also elsewhere on the board
~3BP_CSYNC: IC512.23 (CSYNC); also elsewhere on the board
~AS: IC516.12, IC516.13, R558.2, R559.1, T599.1; also elsewhere on the board
~CAS0: IC515.3 (C); also elsewhere on the board
~MRES: CE520.1, D502.1 (K); also elsewhere on the board
~XAS: IC516.8; also elsewhere on the board
~XRESET: IC511.17 (RESO); also elsewhere on the board
~YS0: IC512.3 (YS); also elsewhere on the board

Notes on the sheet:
PAL
L604 L605 X501 R540 R541 C570 C574 C575 C578
NTSC
10uH 82uH 4.43361875MHz 430 680 68pF 15pF 47pF 82pF
1 2 3 4 5 8 9 10 11
12uH 100uH 3.579545MHz 560 1.2K 47pF 18pF 56pF 100pF
REF
Bridged, cut and place a cap if required
